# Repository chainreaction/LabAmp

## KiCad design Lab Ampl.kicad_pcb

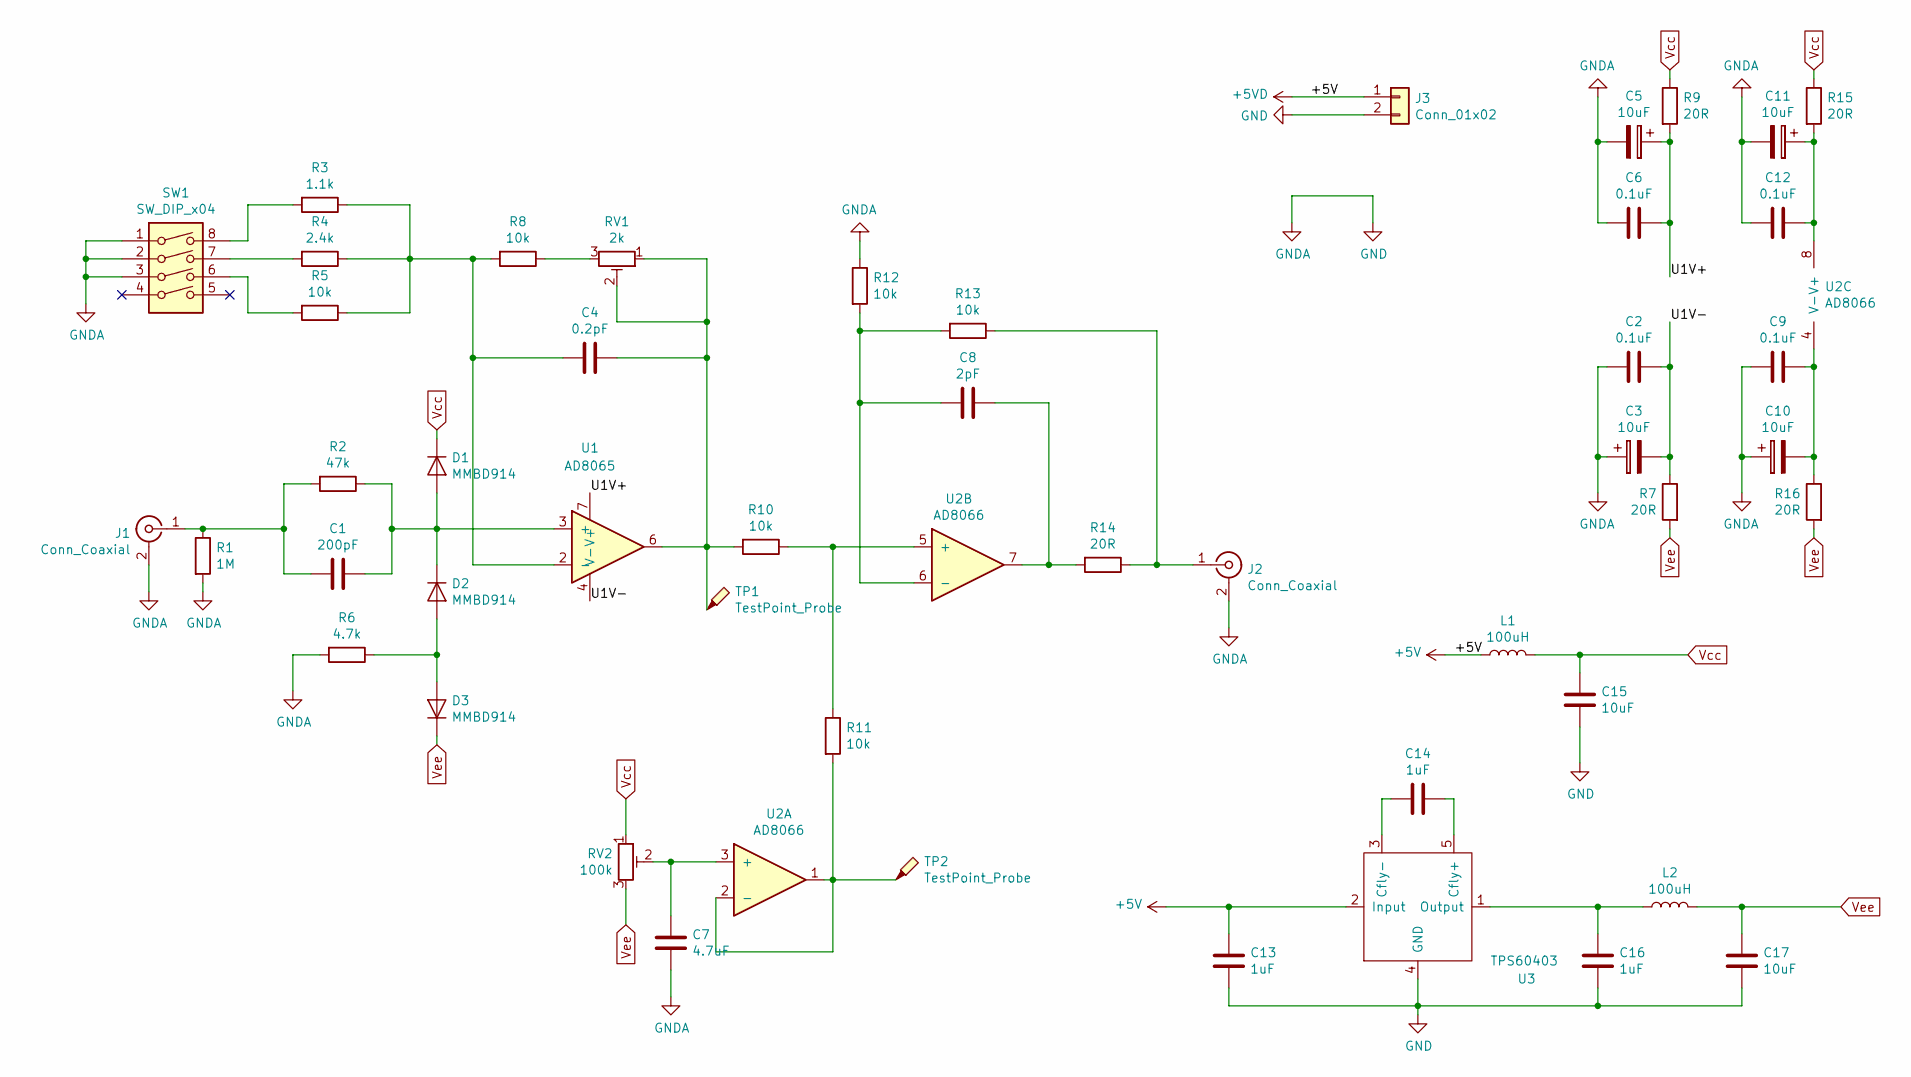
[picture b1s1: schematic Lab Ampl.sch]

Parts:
C1: 200pF; C_0805_2012Metric_Pad1.15x1.40mm_HandSolder
C2, C6, C9, C12: 0.1uF; C_0805_2012Metric_Pad1.15x1.40mm_HandSolder
C3, C5, C10, C11: 10uF; CP_EIA-3528-21_Kemet-B_Pad1.50x2.35mm_HandSolder
C4: 0.2pF; C_0603_1608Metric_Pad1.05x0.95mm_HandSolder
C7: 4.7uF; C_0805_2012Metric_Pad1.15x1.40mm_HandSolder
C8: 2pF; C_0805_2012Metric_Pad1.15x1.40mm_HandSolder
C13, C14, C16: 1uF; C_0805_2012Metric_Pad1.15x1.40mm_HandSolder
C15, C17: 10uF; C_0805_2012Metric_Pad1.15x1.40mm_HandSolder
D1, D2, D3: MMBD914; D_SOT-23_ANK
J1, J2: Conn_Coaxial; My_BNC
J3: Conn_01x02; JST_EH_B02B-EH-A_1x02_P2.50mm_Vertical
L1, L2: 100uH; L_1210_3225Metric
R1: 1M; R_0805_2012Metric_Pad1.15x1.40mm_HandSolder
R2: 47k; R_0805_2012Metric_Pad1.15x1.40mm_HandSolder
R3: 1.1k; R_0805_2012Metric_Pad1.15x1.40mm_HandSolder
R4: 2.4k; R_0805_2012Metric_Pad1.15x1.40mm_HandSolder
R5, R8, R10, R11, R12, R13: 10k; R_0805_2012Metric_Pad1.15x1.40mm_HandSolder
R6: 4.7k; R_0805_2012Metric_Pad1.15x1.40mm_HandSolder
R7, R9, R14, R15, R16: 20R; R_0805_2012Metric_Pad1.15x1.40mm_HandSolder
RV1: 2k; Potentiometer_Bourns_3224W_Vertical
RV2: 100k; Potentiometer_Bourns_3224W_Vertical
SW1: SW_DIP_x04; DIP-8_W8.89mm_SMDSocket_LongPads
TP1, TP2: TestPoint_Probe; TestPoint_Pad_D1.0mm
U1: AD8065; SOIC-8_3.9x4.9mm_P1.27mm
U2: AD8066; SOIC-8_3.9x4.9mm_P1.27mm
U3: TPS60403; SOT-23-5

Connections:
+5V: C13.1, J3.1, L1.1, U3.2 (Input)
/U1V+: C5.1, C6.1, R9.2, U1.7 (V+)
/U1V-: C2.2, C3.2, R7.1, U1.4 (V-)
GND: C2.1, C3.1, C5.2, C6.2, C7.2, C9.1, C10.1, C11.2, C12.2, C13.2, C15.2, C16.2, C17.2, J1.2 (Ext), J2.2 (Ext), J3.2, R1.2, R6.2, R12.1, SW1.1, SW1.2, SW1.3, U3.4 (GND)
unnamed: C1.1, D1.2 (A), D2.1 (K), R2.1, U1.3 (+)
unnamed: C1.2, J1.1 (In), R1.1, R2.2
unnamed: C4.1, R10.2, RV1.1, RV1.2, TP1.1, U1.6
unnamed: C4.2, R3.1, R4.1, R5.1, R8.2, U1.2 (-)
unnamed: C7.1, RV2.2, U2.3 (+)
unnamed: C8.1, R14.2, U2.7
unnamed: C8.2, R12.2, R13.2, U2.6 (-)
unnamed: C9.2, C10.2, R16.1, U2.4 (V-)
unnamed: C11.1, C12.1, R15.2, U2.8 (V+)
unnamed: C14.1, U3.5 (Cfly+)
unnamed: C14.2, U3.3 (Cfly-)
unnamed: C16.1, L2.1, U3.1 (Output)
unnamed: D2.2 (A), D3.2 (A), R6.1
unnamed: J2.1 (In), R13.1, R14.1
unnamed: R3.2, SW1.8
unnamed: R4.2, SW1.7
unnamed: R5.2, SW1.6
unnamed: R8.1, RV1.3
unnamed: R10.1, R11.1, U2.5 (+)
unnamed: R11.2, TP2.1, U2.1, U2.2 (-)
Vcc: C15.1, D1.1 (K), L1.2, R9.1, R15.1, RV2.1
Vee: C17.1, D3.1 (K), L2.2, R7.2, R16.2, RV2.3

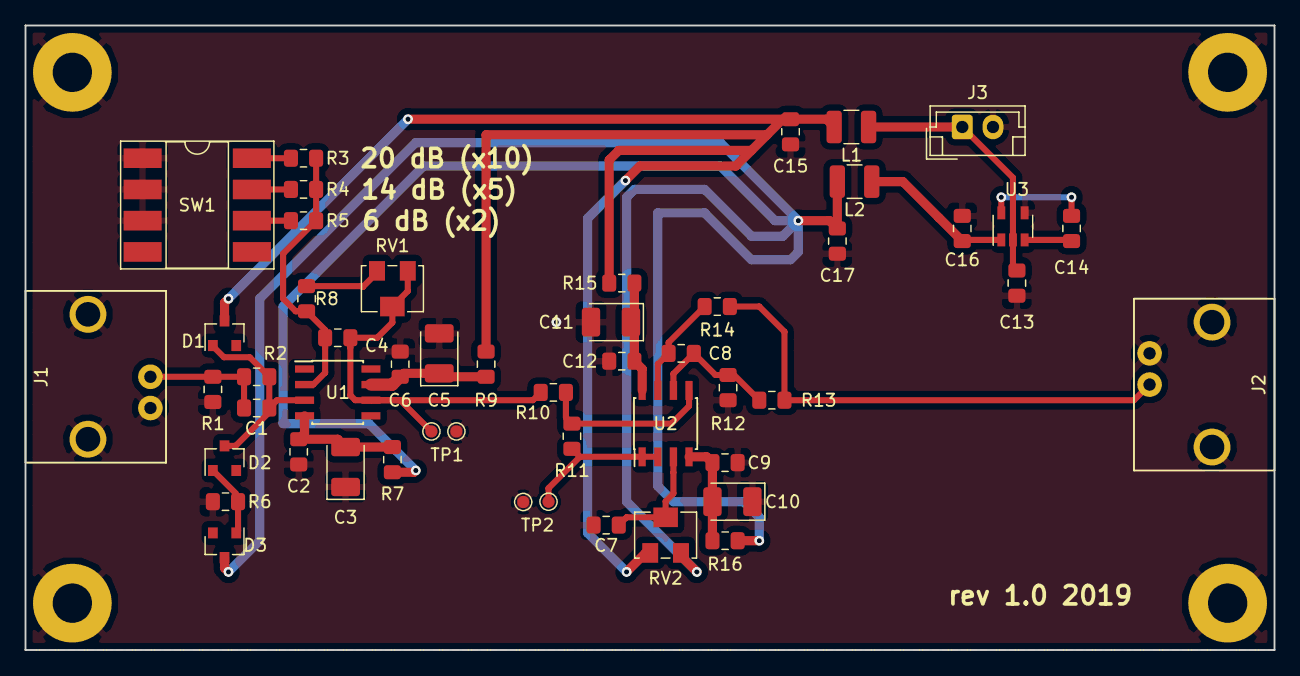
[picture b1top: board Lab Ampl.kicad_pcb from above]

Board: 2 copper layers, 101.6 x 50.8 mm, 49 parts (0 on the bottom side), 26 nets.

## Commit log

2019-03-19 Initial comit for rev. 1.0 board
2019-03-19 Added pdf for the schematics.
